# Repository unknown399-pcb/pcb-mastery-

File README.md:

# Dyn3
A KiCad design made with KiCad Editor.

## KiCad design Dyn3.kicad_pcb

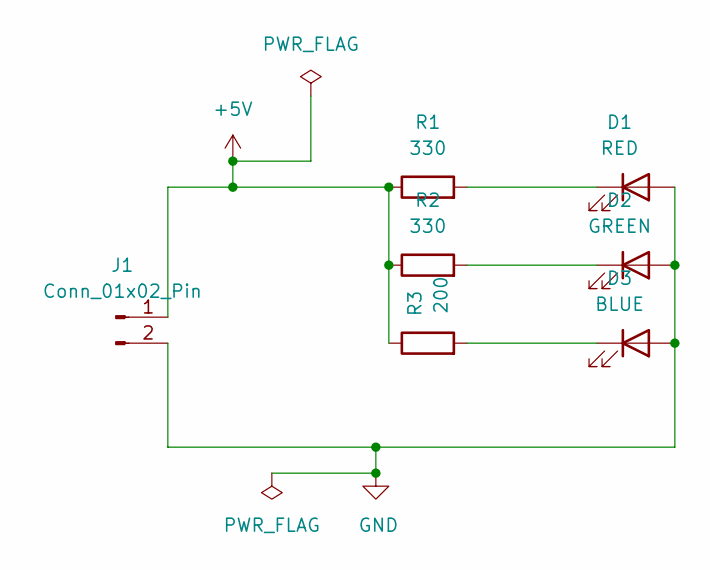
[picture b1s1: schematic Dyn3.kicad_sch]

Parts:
D1: RED; LED_0603_1608Metric
D2: GREEN; LED_0603_1608Metric
D3: BLUE; LED_0603_1608Metric
J1: Conn_01x02_Pin; PinHeader_1x02_P2.54mm_Vertical
R1, R2: 330; R_0603_1608Metric
R3: 200; R_0603_1608Metric

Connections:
+5V: J1.1, R1.1, R2.1, R3.1
GND: D1.2 (A), D2.2 (A), D3.2 (A), J1.2
unnamed: D1.1 (K), R1.2
unnamed: D2.1 (K), R2.2
unnamed: D3.1 (K), R3.2

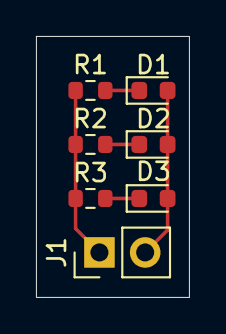
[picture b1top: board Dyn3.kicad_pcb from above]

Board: 2 copper layers, 8.5 x 14.5 mm, 7 parts (0 on the bottom side), 5 nets.
